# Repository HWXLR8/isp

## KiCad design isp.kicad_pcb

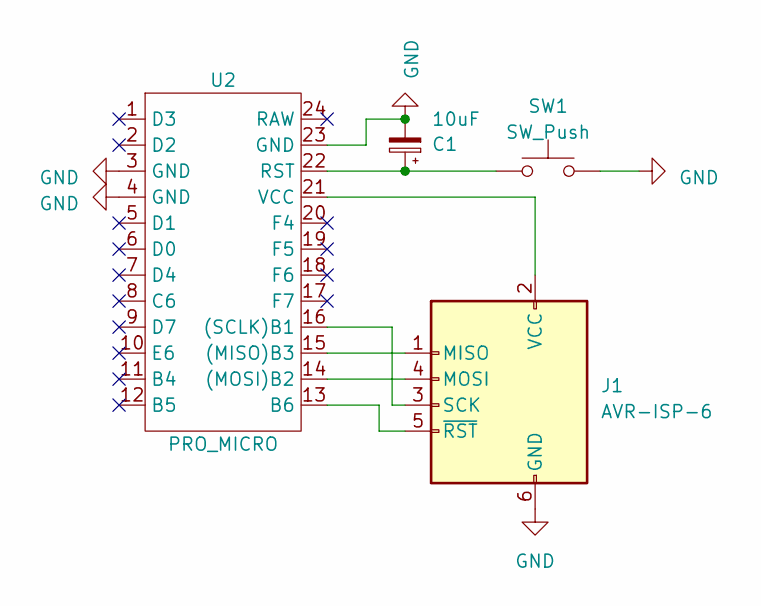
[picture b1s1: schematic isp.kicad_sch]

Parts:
C1: 10uF; CP_Radial_D5.0mm_P2.50mm
J1: AVR-ISP-6; IDC-Header_2x03_P2.54mm_Vertical
SW1: SW_Push; SW_PUSH_6mm
U2: PRO_MICRO; ProMicro-NoSilk

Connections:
GND: C1.2, J1.6 (GND), SW1.2, U2.3 (GND), U2.4 (GND), U2.23 (GND)
unnamed: J1.1 (MISO), U2.15 ((MISO)B3)
unnamed: J1.4 (MOSI), U2.14 ((MOSI)B2)
unnamed: J1.3 (SCK), U2.16 ((SCLK)B1)
unnamed: J1.2 (VCC), U2.21 (VCC)
unnamed: J1.5 (~RST), U2.13 (B6)
unnamed: C1.1, SW1.1, U2.22 (RST)

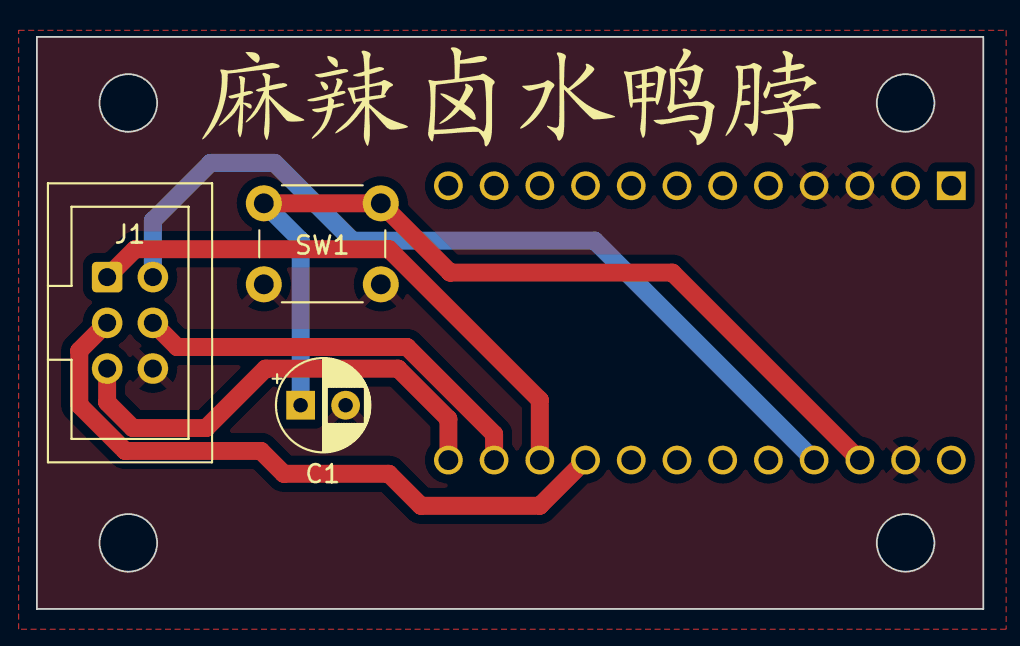
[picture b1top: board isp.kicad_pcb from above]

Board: 2 copper layers, 52.6 x 31.8 mm, 4 parts (0 on the bottom side), 7 nets.

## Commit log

2023-06-17 init
2023-06-20 add breakout header
